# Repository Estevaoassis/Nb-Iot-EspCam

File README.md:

# PROT-TIPO-PARA-CAPTURA-E-TRANSMISS-O-DE-IMAGENS-DE-BAIXA-RESOLU-O-UTILIZANDO-CAT-NB2
Protótipo embarcado para captura e transmissão de imagens de baixa resolução via rede Cat NB2, com foco em baixo consumo energético e conectividade IoT. O sistema utiliza câmera compacta, compressão de dados e envio eficiente para monitoramento remoto em áreas com cobertura limitada.

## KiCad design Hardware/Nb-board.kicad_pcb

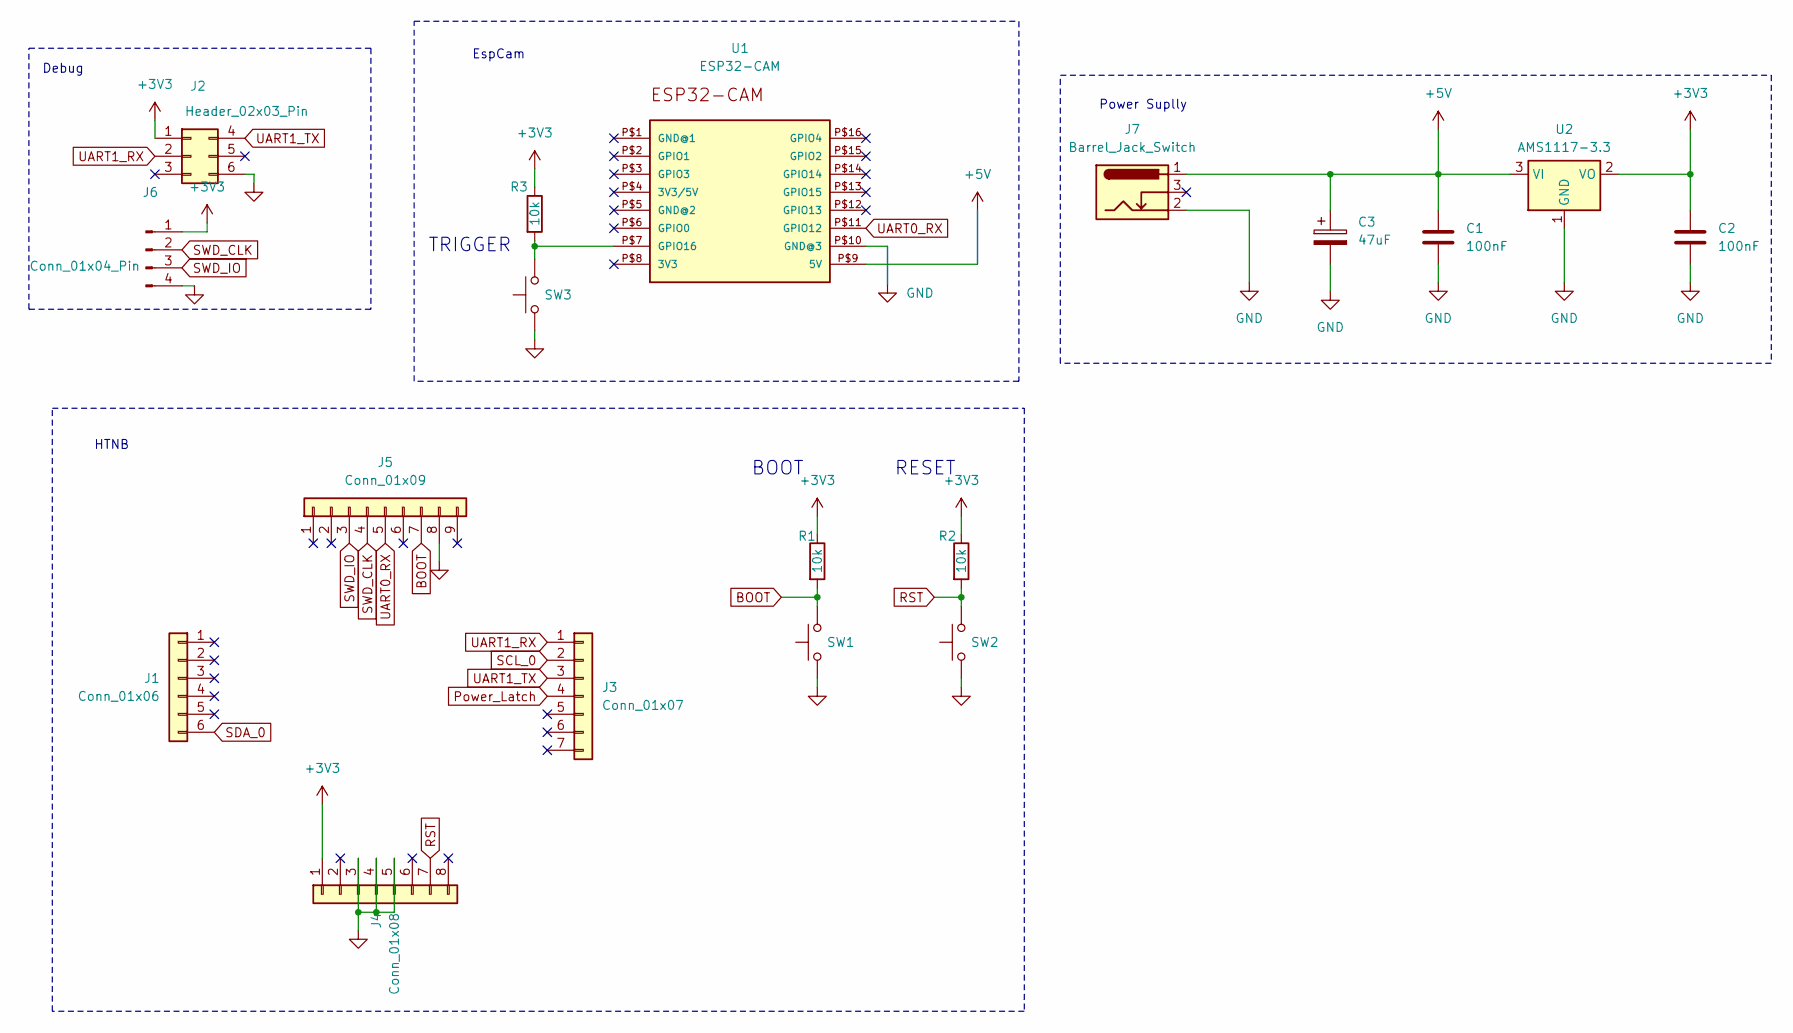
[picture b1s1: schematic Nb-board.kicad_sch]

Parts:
C1, C2: 100nF; C_Disc_D5.0mm_W2.5mm_P5.00mm
C3: 47uF; CP_Radial_D5.0mm_P2.50mm
J1: Conn_01x06; PinSocket_1x06_P2.54mm_Vertical
J2: Header_02x03_Pin; PinHeader_2x03_P2.54mm_Vertical
J3: Conn_01x07; PinSocket_1x07_P2.54mm_Vertical
J4: Conn_01x08; PinSocket_1x08_P2.54mm_Vertical
J5: Conn_01x09; PinSocket_1x09_P2.54mm_Vertical
J6: Conn_01x04_Pin; PinHeader_1x04_P2.54mm_Vertical
J7: Barrel_Jack_Switch; BarrelJack_Horizontal
R1, R2, R3: 10k; R_Axial_DIN0207_L6.3mm_D2.5mm_P10.16mm_Horizontal
SW1, SW2, SW3: SW_Push; SW_PUSH_6mm
U1: ESP32-CAM
U2: AMS1117-3.3; SOT-223-3_TabPin2

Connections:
+3V3: C2.1, J2.1, J4.1, J6.1, R1.1, R2.1, R3.1, U2.2 (VO)
+5V: C1.1, C3.1, J7.1, U1.P$9 (5V), U2.3 (VI)
BOOT: J5.7, R1.2, SW1.2
GND: C1.2, C2.2, C3.2, J2.6, J4.3, J4.4, J4.5, J5.8, J6.4, J7.2, SW1.1, SW2.1, SW3.1, U1.P$10 (GND@3), U2.1 (GND)
unnamed: R3.2, SW3.2, U1.P$7 (GPIO16)
Power_Latch: J3.4
RST: J4.7, R2.2, SW2.2
SCL_0: J3.2
SDA_0: J1.6
SWD_CLK: J5.4, J6.2
SWD_IO: J5.3, J6.3
UART0_RX: J5.5, U1.P$11 (GPIO12)
UART1_RX: J2.2, J3.1
UART1_TX: J2.4, J3.3

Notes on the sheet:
RESET
HTNB
Debug
TRIGGER
EspCam
BOOT
Power Suplly

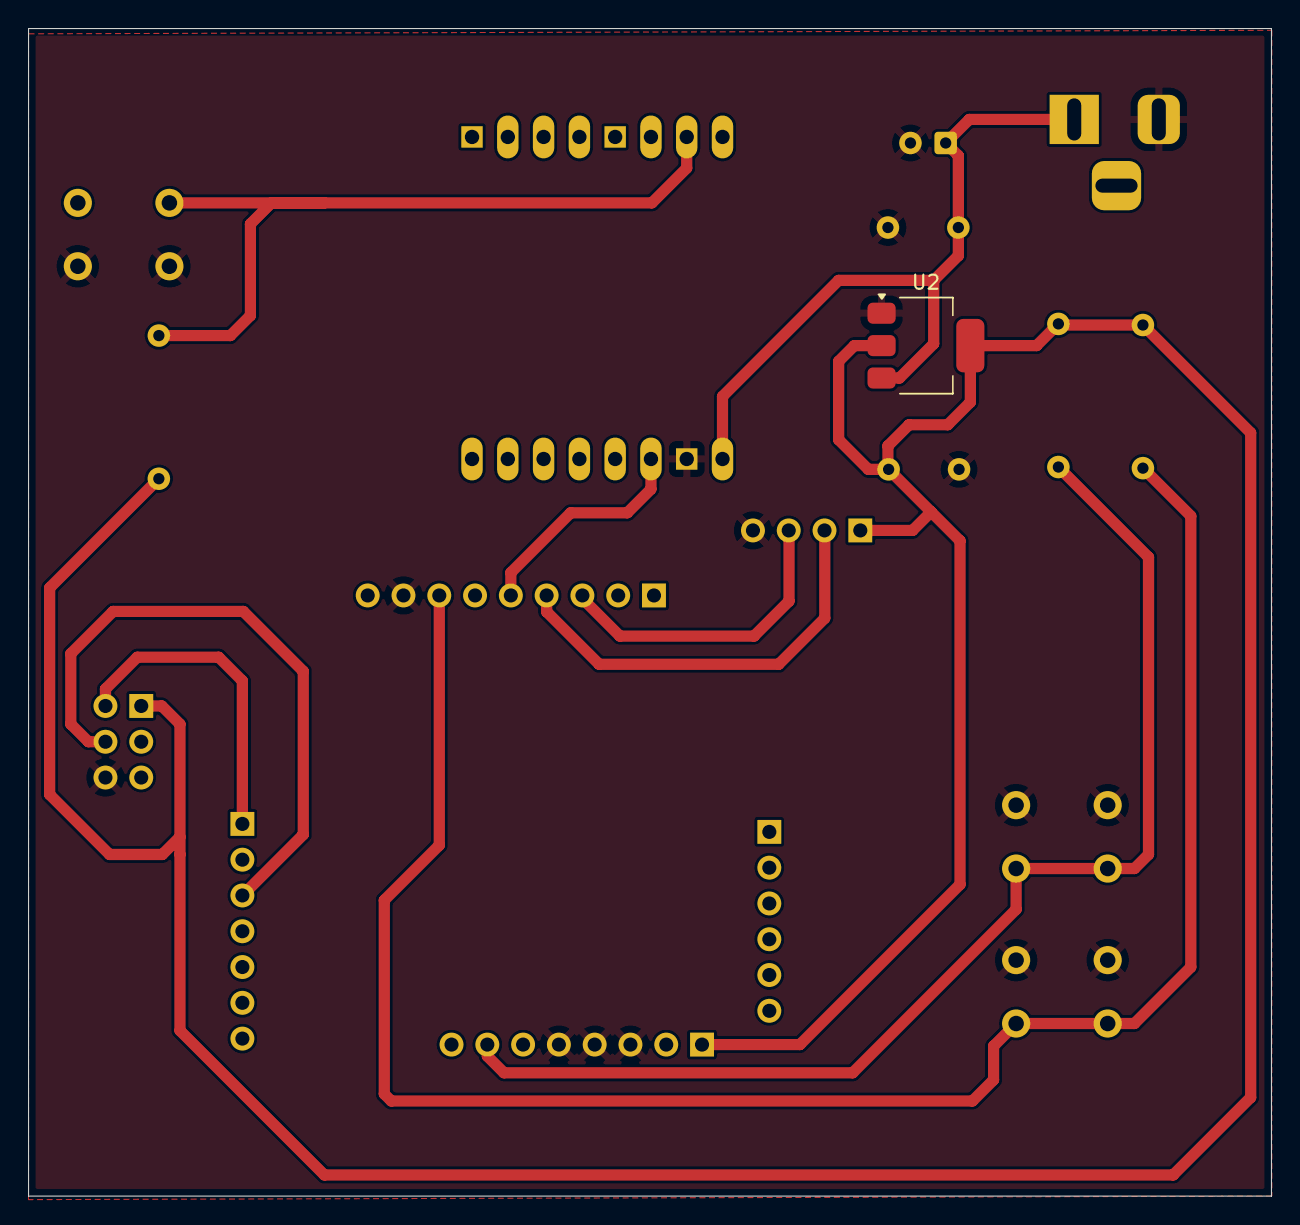
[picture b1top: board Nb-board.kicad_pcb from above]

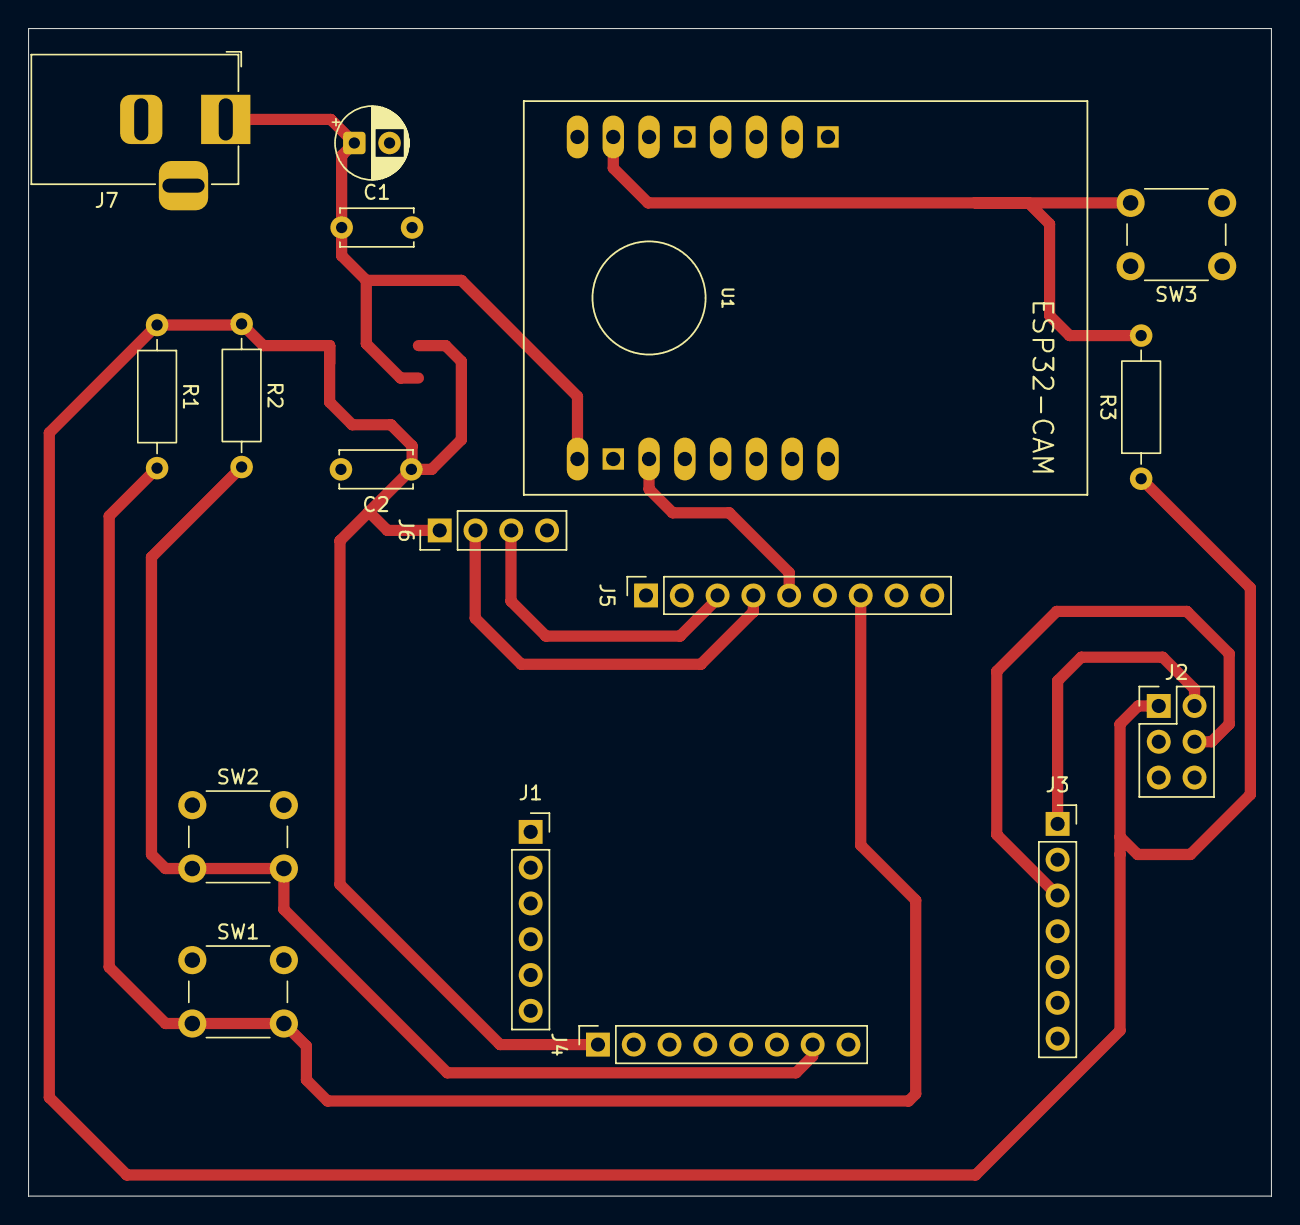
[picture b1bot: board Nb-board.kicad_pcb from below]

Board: 2 copper layers, 88.2 x 82.9 mm, 18 parts (17 on the bottom side), 11 nets.

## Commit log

2026-05-27 Add initial implementation of camera functionality and create README files for documentation
2026-05-27 Add HTNB32L-XXX-SDK as a submodule
2026-05-29 chore: add .gitignore
2026-05-29 chore: add requirements.txt for project dependencies
2026-05-29 feat: add settings configuration for Serial communication and image output
2026-05-29 feat: implement ModemSerial class for serial communication handling
2026-05-29 feat: add executar function for hex string capture and image saving
2026-06-03 chore: add .gitignore file for hardware directory
2026-06-03 feat: add Nb-board v1.0
2026-06-03 feat: reintroduce main.ino for camera initialization and image transmission; update settings for serial communication
2026-06-03 feat: update requirements.txt to include paho-mqtt
2026-06-04 feat: add mqtt_receiver script to reconstruct and save fragmented images from ESP32-CAM
2026-06-08 docs: update software README.md
2026-06-09 feat: implement web dashboard with image gallery and add production hardware manufacturing files
2026-06-09 docs: update README
2026-06-11 chore: add .gitignore files and vscode config
2026-06-11 feat: add examples binaries files
2026-06-11 feat: add HTNB32L SDK OFFICIAL
2026-06-11 feat: add HT_PREBUILDS and MIDDLEWARES LIBS
2026-06-11 feat: add debugs scripts
2026-06-11 feat: add HTNB32L ESP-CAM application
2026-06-11 refactor: delete HTNB32L XX SDK repo
2026-06-11 chore: add makefile
2026-06-11 feat: add project kicad 9.0 board to HTNB32L
2026-06-11 feat: add captures images
